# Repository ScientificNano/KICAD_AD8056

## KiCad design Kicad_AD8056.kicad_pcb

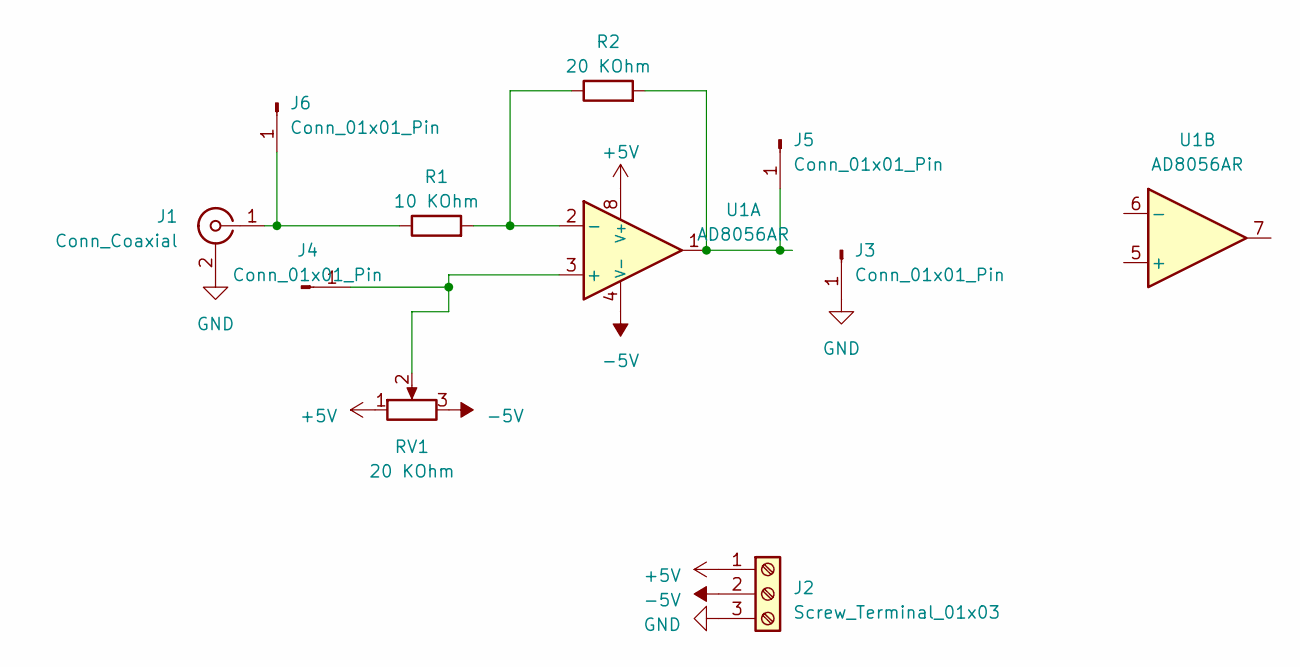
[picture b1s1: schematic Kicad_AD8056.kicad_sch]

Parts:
J1: Conn_Coaxial; U.FL_Hirose_U.FL-R-SMT-1_Vertical
J2: Screw_Terminal_01x03; TerminalBlock_bornier-3_P5.08mm
J3, J4, J5, J6: Conn_01x01_Pin; Pin_D1.0mm_L10.0mm
R1: 10 KOhm; R_0805_2012Metric
R2: 20 KOhm; R_0805_2012Metric
RV1: 20 KOhm; Potentiometer_Alps_RK163_Single_Horizontal
U1: AD8056AR; SSOP-8_3.9x5.05mm_P1.27mm

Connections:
+5V: J2.1, RV1.1, U1.8 (V+)
-5V: J2.2, RV1.3, U1.4 (V-)
GND: J1.2 (Ext), J2.3, J3.1
unnamed: J1.1 (In), J6.1, R1.1
unnamed: J4.1, RV1.2, U1.3 (+)
unnamed: J5.1, R2.2, U1.1
unnamed: R1.2, R2.1, U1.2 (-)

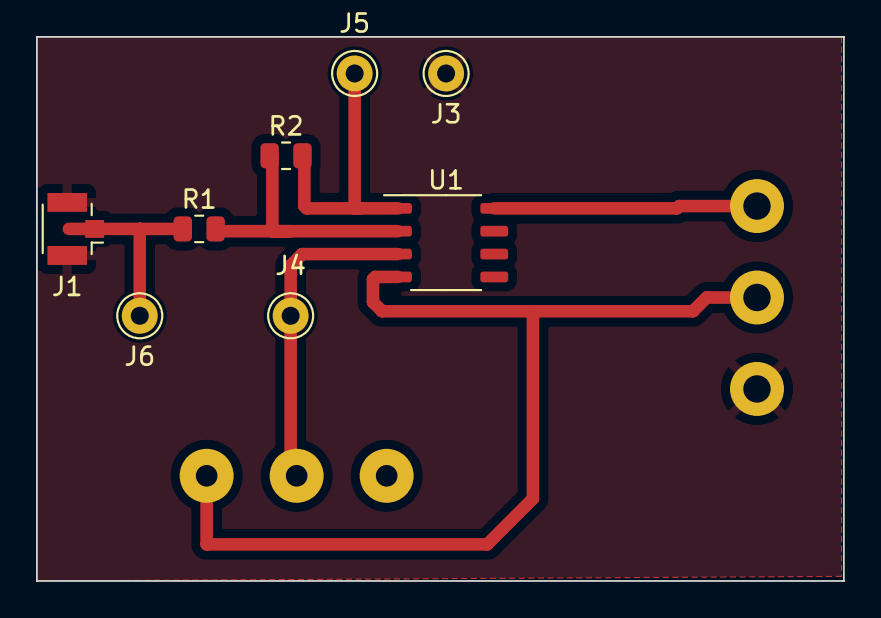
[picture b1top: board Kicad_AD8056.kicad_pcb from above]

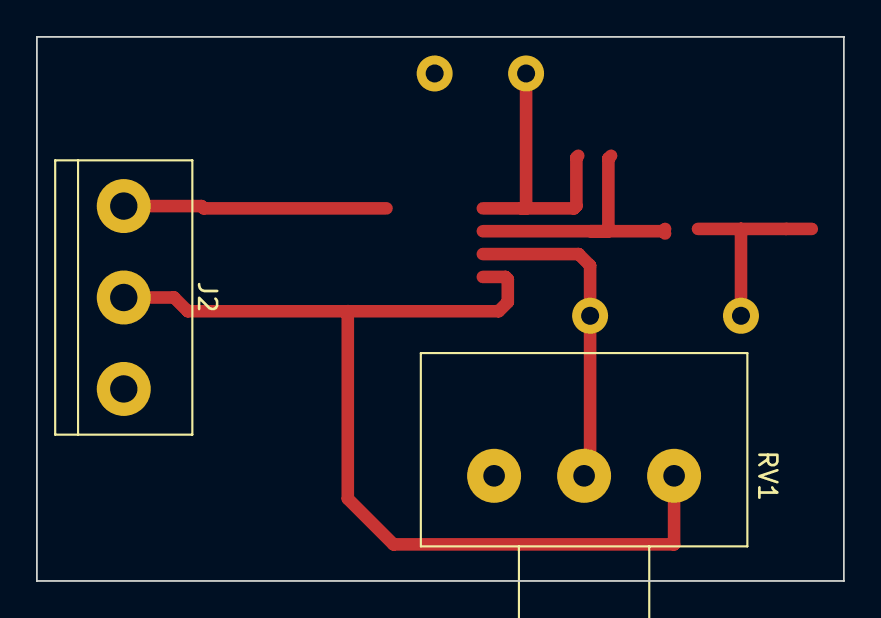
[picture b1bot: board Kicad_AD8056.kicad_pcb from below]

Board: 2 copper layers, 44.8 x 30.2 mm, 10 parts (2 on the bottom side), 7 nets.

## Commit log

2023-09-22 ad8086
2023-09-27 add new pcb
2023-09-27 add new pcb prototype
2023-09-27 new pcb prototype №1
